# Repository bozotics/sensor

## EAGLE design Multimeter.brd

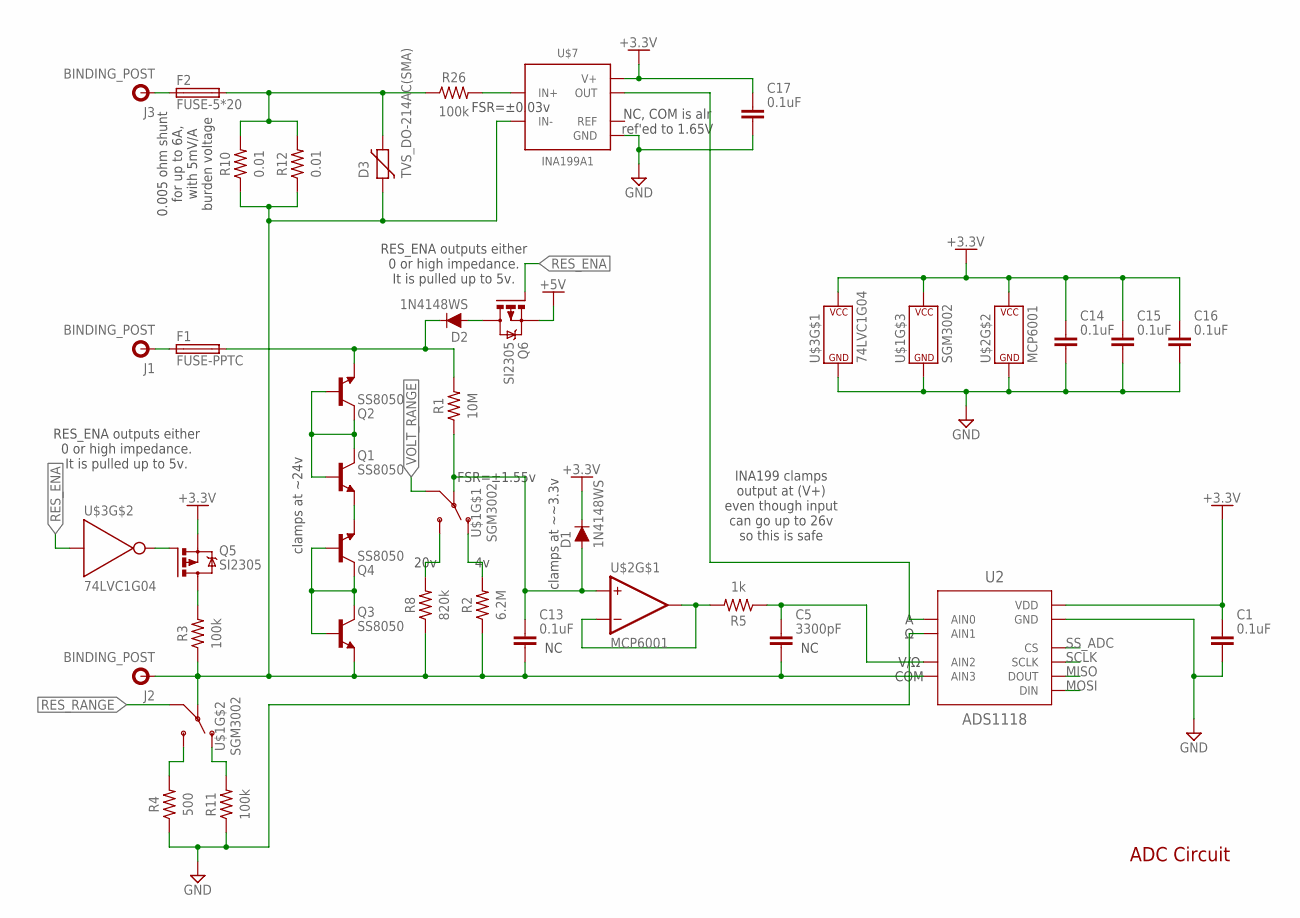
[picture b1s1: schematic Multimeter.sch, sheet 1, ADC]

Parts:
C1, C13, C14, C15, C16, C17: 0.1uF; CAPC1608X85
C5: 3300pF; CAPC1608X85
D1, D2: 1N4148WS; SOD-323
D3: TVS_DO-214AC(SMA); DIOM5226X290N
F1: FUSE-PPTC; FUSE-PPTC-TH
F2: FUSE-5*20; FUSEHOLDER_"HD"
J1, J2, J3: BINDING_POST
Q1, Q2, Q3, Q4: SS8050; SOT95P237X112-3N
Q5, Q6: SI2305; SOT23
R1: 10M; RESC1608X60
R2: 6.2M; RESC1608X60
R3, R11, R26: 100k; RESC1608X60
R4: 500; RESC1608X60
R5: 1k; RESC1608X60
R8: 820k; RESC1608X60
R10, R12: 0.01; RESC6332X71
U2: ADS1118; VSSOP10
U$1: SGM3002; MSOP10
U$2: MCP6001; SOT23-5
U$3: 74LVC1G04; SOT23-5
U$7: INA199A1; SC70-6

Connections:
+3.3V: C1.1, C14.1, C15.1, C16.1, C17.1, D1.C, Q5.2 (S), U2.8 (VDD), U$1.8 (P$V+), U$2.5 (P$V+), U$3.5 (P$V+), U$7.3 (V+); also elsewhere on the board
+5V: Q6.2 (S); also elsewhere on the board
COM: C5.2, C13.2, D3.1, J2.P$1, Q3.1 (E), R2.1, R3.1, R8.1, R10.1, R12.1, U2.7 (AIN3), U$1.6 (COM), U$7.5 (IN-)
GND: C1.2, C14.2, C15.2, C16.2, C17.2, R4.1, R11.1, U2.3 (GND), U2.5 (AIN1), U$1.3 (P$V-), U$2.2 (P$V-), U$3.3 (P$V-), U$7.2 (GND); also elsewhere on the board
MISO: U2.9 (DOUT); also elsewhere on the board
MOSI: U2.10 (DIN); also elsewhere on the board
unnamed: D2.C, F1.P$2 (2), Q2.1 (E), R1.2
unnamed: C13.1, D1.A, R1.1, U$1.10 (COM), U$2.3 (+IN)
unnamed: D2.A, Q6.3 (D)
unnamed: Q3.2 (B), Q3.3 (C), Q4.2 (B), Q4.3 (C)
unnamed: F2.P$1 (1), J3.P$1
unnamed: R5.2, U$2.1 (OUT), U$2.4 (-IN)
unnamed: C5.1, R5.1, U2.6 (AIN2)
unnamed: U2.4 (AIN0), U$7.6 (OUT)
unnamed: R4.2, U$1.4 (NO)
unnamed: R8.2, U$1.2 (NO)
unnamed: R2.2, U$1.9 (NC)
unnamed: Q1.2 (B), Q1.3 (C), Q2.2 (B), Q2.3 (C)
unnamed: Q1.1 (E), Q4.1 (E)
unnamed: F1.P$1 (1), J1.P$1
unnamed: R11.2, U$1.7 (NC)
unnamed: D3.2, F2.P$2 (2), R10.2, R12.2, R26.1
unnamed: Q5.3 (D), R3.2
unnamed: Q5.1 (G), U$3.4 (Y)
unnamed: R26.2, U$7.4 (IN+)
RES_ENA: Q6.1 (G), U$3.2 (A); also elsewhere on the board
RES_RANGE: U$1.5 (IN); also elsewhere on the board
SCLK: U2.1 (SCLK); also elsewhere on the board
SS_ADC: U2.2 (CS); also elsewhere on the board
VOLT_RANGE: U$1.1 (IN); also elsewhere on the board

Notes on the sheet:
clamps at ~24v
V/Ω
COM
20v
RES_ENA outputs either 0 or high impedance. It is pulled up to 5v.
clamps at ~~3.3v
0.005 ohm shunt for up to 6A, with 5mV/A burden voltage
NC, COM is alr ref'ed to 1.65V
FSR=±1.55v
FSR=±0.03v
INA199 clamps output at (V+) even though input can go up to 26v so this is safe
ADC Circuit

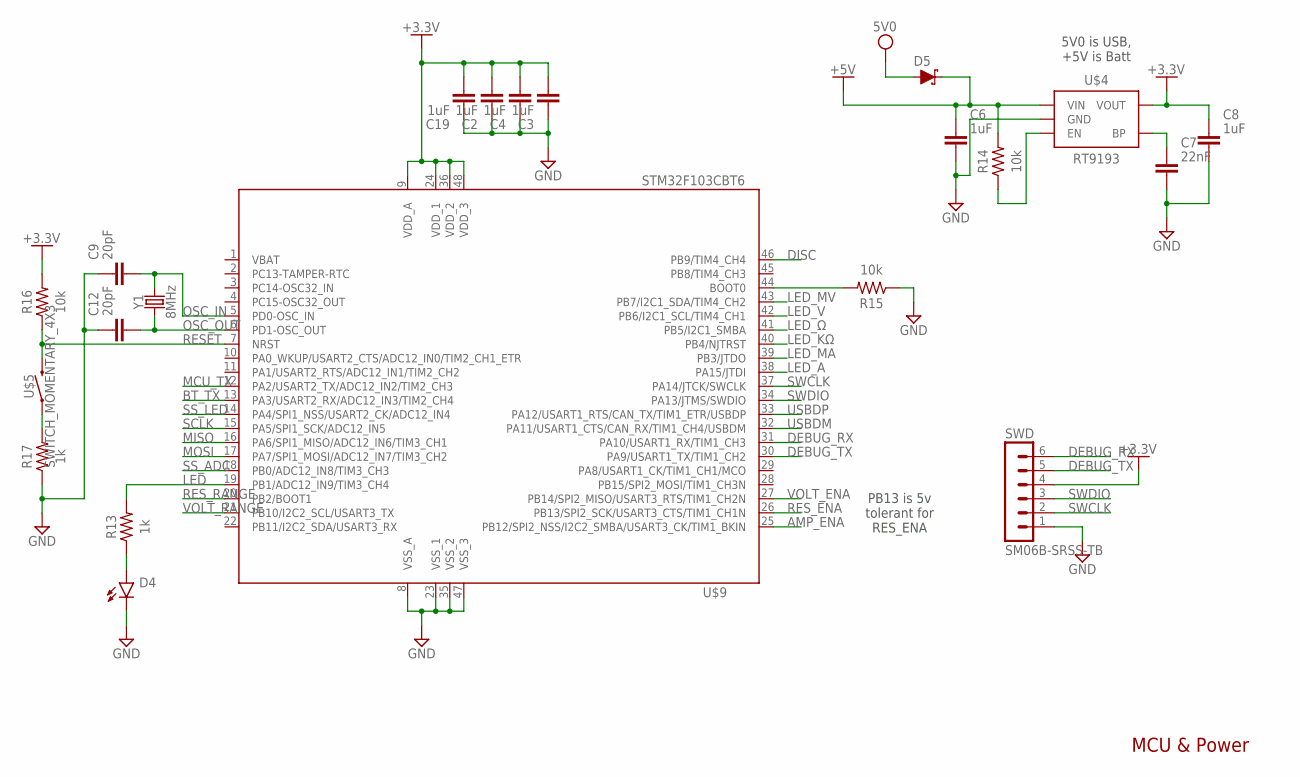
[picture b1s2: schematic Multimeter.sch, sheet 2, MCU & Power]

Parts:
C2, C3, C4, C6, C8, C19: 1uF; CAPC1608X85
C7: 22nF; CAPC1608X85
C9, C12: 20pF; CAPC1608X85
D4: LED_CHIP_BLUE-1608; LEDC1608X39N_B
D5: DIODE-SCHOTTKY; SMA-DIODE
R13, R17: 1k; RESC1608X60
R14, R15, R16: 10k; RESC1608X60
SWD: SM06B-SRSS-TB
U$4: RT9193; SOT23-5
U$5: SWITCH_MOMENTARY_4X3; MOMENTARY_SWITCH_4X3
U$9: STM32F103CBT6; LQFP48
Y1: 8MHz; CRYSTAL-SMD-5X3.2-2PAD

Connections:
5V0: D5.A; also elsewhere on the board
+3.3V: C2.2, C3.2, C4.2, C8.1, C19.2, R16.2, SWD.4, U$4.5 (VOUT), U$9.9 (VDD_A), U$9.24 (VDD_1), U$9.36 (VDD_2), U$9.48 (VDD_3); also elsewhere on the board
+5V: C6.1, D5.C, R14.2, U$4.1 (VIN); also elsewhere on the board
AMP_ENA: U$9.25 (PB12/SPI2_NSS/I2C2_SMBA/USART3_CK/TIM1_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); also elsewhere on the board
BT_TX: U$9.13 (PA3/USART2_RX/ADC12_IN3/TIM2_CH4); also elsewhere on the board
DEBUG_RX: SWD.6, U$9.31 (PA10/USART1_RX/TIM1_CH3)
DEBUG_TX: SWD.5, U$9.30 (PA9/USART1_TX/TIM1_CH2)
DISC: U$9.46 (PB9/TIM4_CH4); also elsewhere on the board
GND: C2.1, C3.1, C4.1, C6.2, C7.2, C8.2, C9.1, C12.1, C19.1, D4.2 (C), R15.1, R17.1, SWD.1, U$4.2 (GND), U$9.8 (VSS_A), U$9.23 (VSS_1), U$9.35 (VSS_2), U$9.47 (VSS_3); also elsewhere on the board
LED: R13.2, U$9.19 (PB1/ADC12_IN9/TIM3_CH4)
LED_A: U$9.38 (PA15/JTDI); also elsewhere on the board
LED_KΩ: U$9.40 (PB4/NJTRST); also elsewhere on the board
LED_MA: U$9.39 (PB3/JTDO); also elsewhere on the board
LED_MV: U$9.43 (PB7/I2C1_SDA/TIM4_CH2); also elsewhere on the board
LED_V: U$9.42 (PB6/I2C1_SCL/TIM4_CH1); also elsewhere on the board
LED_Ω: U$9.41 (PB5/I2C1_SMBA); also elsewhere on the board
MCU_TX: U$9.12 (PA2/USART2_TX/ADC12_IN2/TIM2_CH3); also elsewhere on the board
MISO: U$9.16 (PA6/SPI1_MISO/ADC12_IN6/TIM3_CH1); also elsewhere on the board
MOSI: U$9.17 (PA7/SPI1_MOSI/ADC12_IN7/TIM3_CH2); also elsewhere on the board
unnamed: D4.1 (A), R13.1
unnamed: R14.1, U$4.3 (EN)
unnamed: C7.1, U$4.4 (BP)
unnamed: R17.2, U$5.P$1 (1)
unnamed: R15.2, U$9.44 (BOOT0)
OSC_IN: C9.2, U$9.5 (PD0-OSC_IN), Y1.P$2 (2)
OSC_OUT: C12.2, U$9.6 (PD1-OSC_OUT), Y1.P$1 (1)
RESET: R16.1, U$5.P$2 (2), U$9.7 (NRST)
RES_ENA: U$9.26 (PB13/SPI2_SCK/USART3_CTS/TIM1_CH1N); also elsewhere on the board
RES_RANGE: U$9.20 (PB2/BOOT1); also elsewhere on the board
SCLK: U$9.15 (PA5/SPI1_SCK/ADC12_IN5); also elsewhere on the board
SS_ADC: U$9.18 (PB0/ADC12_IN8/TIM3_CH3); also elsewhere on the board
SS_LED: U$9.14 (PA4/SPI1_NSS/USART2_CK/ADC12_IN4); also elsewhere on the board
SWCLK: SWD.2, U$9.37 (PA14/JTCK/SWCLK)
SWDIO: SWD.3, U$9.34 (PA13/JTMS/SWDIO)
USBDM: U$9.32 (PA11/USART1_CTS/CAN_RX/TIM1_CH4/USBDM); also elsewhere on the board
USBDP: U$9.33 (PA12/USART1_RTS/CAN_TX/TIM1_ETR/USBDP); also elsewhere on the board
VBAT: U$9.1 (VBAT)
VOLT_ENA: U$9.27 (PB14/SPI2_MISO/USART3_RTS/TIM1_CH2N); also elsewhere on the board
VOLT_RANGE: U$9.21 (PB10/I2C2_SCL/USART3_TX); also elsewhere on the board

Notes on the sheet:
5V0 is USB, +5V is Batt
MCU & Power
PB13 is 5v tolerant for RES_ENA

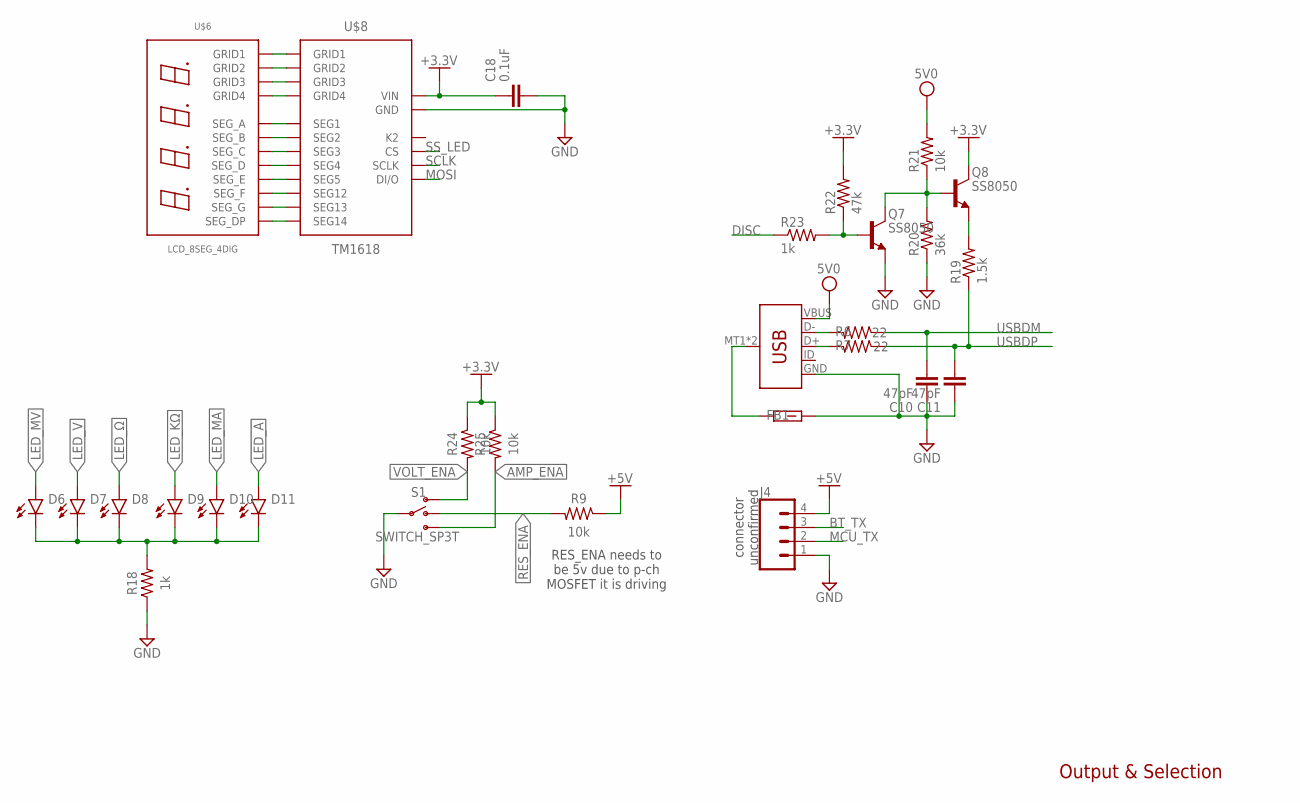
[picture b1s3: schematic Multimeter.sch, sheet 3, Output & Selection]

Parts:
C10, C11: 47pF; CAPC1608X85
C18: 0.1uF; CAPC1608X85
D6, D7, D8, D9, D10, D11: LED_CHIP_BLUE-1608; LEDC1608X39N_B
FB1: 1k; BEADC1608X95N
J4: CONN_04LOCK; 1X04_LOCK
Q7, Q8: SS8050; SOT95P237X112-3N
R6, R7: 22; RESC1608X60
R9, R21, R24, R25: 10k; RESC1608X60
R18, R23: 1k; RESC1608X60
R19: 1.5k; RESC1608X60
R20: 36k; RESC1608X60
R22: 47k; RESC1608X60
S1: SWITCH_SP3T
U$6: LCD_8SEG_4DIG; LCD_8SEG_4DIG_0.4IN
U$8: TM1618; SOP-18
X1: USB-MINIB; USB-MICROB-CLEANED

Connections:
5V0: R21.2, X1.VBUS; also elsewhere on the board
+3.3V: C18.1, Q8.3 (C), R22.2, R24.1, R25.1, U$8.P5 (VIN); also elsewhere on the board
+5V: J4.4, R9.1; also elsewhere on the board
AMP_ENA: R25.2, S1.4; also elsewhere on the board
BT_TX: J4.3; also elsewhere on the board
DISC: R23.1; also elsewhere on the board
GND: C10.1, C11.1, C18.2, FB1.2, J4.1, Q7.1 (E), R18.1, R20.1, S1.3, U$8.P16 (GND), X1.GND; also elsewhere on the board
LED_A: D11.1 (A); also elsewhere on the board
LED_KΩ: D9.1 (A); also elsewhere on the board
LED_MA: D10.1 (A); also elsewhere on the board
LED_MV: D6.1 (A); also elsewhere on the board
LED_V: D7.1 (A); also elsewhere on the board
LED_Ω: D8.1 (A); also elsewhere on the board
MCU_TX: J4.2; also elsewhere on the board
MOSI: U$8.P1 (DI/O); also elsewhere on the board
unnamed: FB1.1, X1.MT1 (SHIELD), X1.MT2 (SHIELD)
unnamed: U$6.11 (SEG_A), U$8.P6 (SEG1)
unnamed: U$6.7 (SEG_B), U$8.P7 (SEG2)
unnamed: U$6.4 (SEG_C), U$8.P8 (SEG3)
unnamed: U$6.2 (SEG_D), U$8.P9 (SEG4)
unnamed: U$6.1 (SEG_E), U$8.P10 (SEG5)
unnamed: U$6.10 (SEG_F), U$8.P11 (SEG12)
unnamed: U$6.5 (SEG_G), U$8.P12 (SEG13)
unnamed: U$6.3 (SEG_DP), U$8.P13 (SEG14)
unnamed: U$6.6 (GRID4), U$8.P14 (GRID4)
unnamed: U$6.8 (GRID3), U$8.P15 (GRID3)
unnamed: U$6.9 (GRID2), U$8.P17 (GRID2)
unnamed: U$6.12 (GRID1), U$8.P18 (GRID1)
unnamed: D6.2 (C), D7.2 (C), D8.2 (C), D9.2 (C), D10.2 (C), D11.2 (C), R18.2
unnamed: Q8.1 (E), R19.2
unnamed: R6.2, X1.D-
unnamed: R7.2, X1.D+
unnamed: Q7.3 (C), Q8.2 (B), R20.2, R21.1
unnamed: Q7.2 (B), R22.1, R23.2
RES_ENA: R9.2, S1.2; also elsewhere on the board
SCLK: U$8.P2 (SCLK); also elsewhere on the board
SS_LED: U$8.P3 (CS); also elsewhere on the board
USBDM: C10.2, R6.1; also elsewhere on the board
USBDP: C11.2, R7.1, R19.1; also elsewhere on the board
VOLT_ENA: R24.2, S1.1; also elsewhere on the board

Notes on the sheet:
Output & Selection
RES_ENA needs to be 5v due to p-ch MOSFET it is driving
connector unconfirmed

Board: 2 copper layers, 85 parts (0 on the bottom side), 77 nets, no tracks yet.

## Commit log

2020-06-14 initial but it's basically done
2020-06-18 add gitattributes

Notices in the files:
parts and their libraries:
Connectors: Licensing: Creative Commons ShareAlike 4.0 International - https://creativecommons.org/licenses/by-sa/4.0
